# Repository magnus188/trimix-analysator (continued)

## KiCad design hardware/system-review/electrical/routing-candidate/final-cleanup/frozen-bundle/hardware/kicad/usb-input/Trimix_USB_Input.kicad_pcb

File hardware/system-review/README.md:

# Trimix whole-system review

**Prototype order status: HOLD.** The main PCB is fully routed and its frozen native DRC reports zero violations, unconnected items and schematic-parity issues. This package records the corrections and reproducible digital evidence; it is not a fabrication release. Factory processes, power-entry and protection evidence, and actual component interfaces must close before ordering. Physical charging, temperature, sealing, module-fit and reference-gas tests have not been performed.

The approved A3 exterior and the original PCBFit baseline are preserved. Mechanical review copies are **Trimix_Enclosure_A3_SystemReview** and the newer **Trimix_Enclosure_A3_ConnectorReview**. Purchasing, showcase work and production printing remain paused.

**2026-09-08 integration update:** the owner supplied a rear photograph with device-up confirmed and measured **13.4 mm from front glass to bare header tips**. The photo locates the Guition header and both USB ports at the top and the onboard SD socket at the left. The [photo registration](integration-photo/README.md) and [saved/reopened ConnectorReview v3](mechanical/connector-review/README.md) supersede the old illustrative connector locations. Complete mate allocations expose interference with the housing, carrier and holder; several straight cable plugs also leave inadequate wire-bend space. Local correction candidates are unadopted, and card service remains unqualified. Earlier v11 clearances do not prove fit of these interfaces. [Optional SD logging](software/sd-card/README.md) is implemented and digitally verified, using the onboard socket. The [bench-equipment record](lab-equipment.md) includes the confirmed multimeter, scope, DC PSU, DL24/P, DLA and FNB58.

The current main board is the reviewed `0962ad86` revision. Its charger bootstrap/REGN and CO-converter feedback/output-capacitor paths were shortened, while all 29 previously checked power/monitor paths were preserved. The [scoped power-layout review](electrical/routing-candidate/sensitive-layout-refinement/root-final-review/README.md) and independent manufacturing checks pass. The former routed revision remains archived. Regulator stability, noise, startup and thermal performance still require physical evidence.

The preserved **SystemReview v11 baseline** is saved and its native archive reopens with the same geometry, parameters and assembly associations. It retains the approved 85 × 180 × 43 mm exterior and exact CNC Kitchen insert models. Two carrier through-openings clear the revised rear components with complete local 2 mm material borders. Its selected component, connector, service, gas and fastener allocations pass at 85 and 87 mm widths, with the intended 85 mm design restored. Both oxygen reference configurations pass their bounded checks. See the [v11 checkpoint](mechanical/final-local-checkpoint/final-handoff.json). The later ConnectorReview findings above take precedence for actual Guition mating and cable-space decisions.

Both P4 firmware builds pass, alongside **53 normal and 53 sanitized host tests**, 98 repository checks and 22 static-analysis units. The [current source-bound software receipt](software/sd-card/evidence/receipt.json) includes SD fault/race tests, shared card/C6 controller lifecycle checks and real LVGL navigation regressions. The current schematic/firmware contract passes 70 assertions. CO requires fresh chamber temperature/humidity within its documented range; invalid conditions clear its displayed value while oxygen and helium stay independent. The [CO verification](software/co-environment/README.md) records scoped tests and [manufacturer use restrictions](electrical/co-module-use-review.md). The CO module remains experimental and cannot certify breathing-gas safety.

Analysis and calibration record results, raw samples and events automatically. The result log identifies both applied O2 and He calibration revisions; concurrent saves cannot mislabel those converted values. Card faults remain separate from NVS settings/calibration. SD safe eject, failed unmounts, session transitions and shutdown preparation have digital coverage. Real card operation, simultaneous radio traffic, memory headroom, write-current peaks and abrupt-power-loss behavior remain physical checks.

The preserved v11 STEP is a reference export with a documented limitation (CAD09): body count, bounds and selected surface/section checks pass, but strict volume comparison and one underlying-plane correspondence do not establish full per-body equivalence. It also predates the photo-correct Guition details. Native Fusion checkpoints carry their own revision and source scope; the old STEP is not the new connector model.

Eight preserved v11 PLA/PETG diagnostic projects for four printed parts pass 50 slice checks. These are fit-study files, with support removal, printed dimensions, retention, sealing and temperature tests still pending. They do not qualify the later proposed carrier or harness changes. [The acceptance ledger](acceptance.csv) separates completed digital work from the **13 remaining order-blocking gates**; those gates are related and are not 13 demonstrated hardware failures.

## Read the package

| Area | Starting document / evidence |
|---|---|
| Check-by-check acceptance and unresolved gates | [Acceptance ledger](acceptance.csv) — scoped statuses and the remaining order gates |
| Electrical interface, pin audits and calculations | [Electrical review](electrical/README.md), [logical interface](electrical/interface-contract.md) |
| Exact purchasing and assembly populations | [Part qualification ledger](electrical/part-qualification.csv) — unresolved entries are not purchasing approval |
| USB source rules and legacy limitations | [Current USB-IF source review](electrical/usb-default-current-review/README.md), [limiter alternatives and rejected assumptions](electrical/usb-protection-research/transient-options/README.md) |
| Screen cable and power entry | [Matched harness review](electrical/host-harness-review/README.md), [Guition power and service isolation](electrical/host-power-review/README.md) |
| Fabrication and routing | [Manufacturing constraints](electrical/manufacturing-and-routing.md), [selected stackup](electrical/stackup-review.md), fresh ERC/DRC JSON files in `electrical/` |
| Current main-board files | [Routed main delivery index](electrical/main-final/README.md) — Gerbers, drills, factory/manual BOMs, factory-only stencil, marking guide and selected-hole process map; order HOLD |
| Independent manufacturing-file review | [Final CAM review](electrical/main-final-independent/final-0962ad86/README.md) — 44 geometry/connectivity, 20 assembly-ledger, 12 preservation and 50 process checks pass; supplier process approval remains pending |
| Frozen routed main PCB | [Independent final power and ground review](electrical/routing-candidate/sensitive-layout-refinement/root-final-review/README.md) — 29 prior power/monitor paths retained, 35 local routes connected, one connected In1 reference and no lost ground contacts; physical performance remains unqualified |
| Completed controls checkpoint | [Parent review of the controls and power paths](electrical/routing-candidate/complete-controls-root-review/README.md) — preserved intermediate source before final assembly cleanup |
| Earlier routing evidence | [USB voltage-monitor and input-trace review](electrical/routing-candidate/monitor-root-review/README.md), [charger interrupt and I²C pull-ups](electrical/routing-candidate/cap-signal-reconnect/pullup-swap/README.md) — preserved intermediate checkpoints |
| Latest protection-chip escape | [CC route, retained voltage-setting circuit and ground checks](electrical/routing-candidate/set-cc-root-proposal/vippo-cc/README.md), [independent mask/drill and rule controls](electrical/vippo-process-review/native-v3-independent/README.md) — scoped proof; combined routing and factory process acceptance remain open |
| Copper-path diagnostic | [Method and limits](electrical/current-path-review/README.md), [preserved prior-board native path inventory](electrical/routing-candidate/final-cleanup/root-review/current-paths/paths.csv) — geometry sensitivities, not equivalent resistance or current ratings |
| Supplier questions prepared for later use | [Unsent process-review request](electrical/supplier-review-request.md) — no supplier contacted or order placed |
| Mechanical model and measurements | [Current enclosure review](mechanical/README.md), [final saved assembly](mechanical/final-local-checkpoint/final-handoff.json), [measurement checklist](mechanical/MEASUREMENTS.md) — provisional models stay labelled |
| Oxygen setup and calibration | [Oxygen implementation and UI evidence](software/oxygen/README.md) |
| OTA, storage and maintenance | [OTA review](software/ota/README.md), [concurrent-save evidence](software/ota/storage-maintenance-race-verification.json) |
| Onboard SD recording and shared controller | [Use, implementation and limits](software/sd-card/README.md), [final source-bound receipt](software/sd-card/evidence/receipt.json), [independent receipt binding check](integration-photo/sd-software-binding-check.json) |
| Production sensor, power and environmental acquisition | [Firmware integration](software/README.md), [input isolation and charging standby](software/power/input-isolation/README.md), [legacy attachment endurance](software/power/input-isolation/legacy-endurance-review/README.md) |
| Combined tests and firmware builds | `verification/` — source hashes must match the reported build and check |
| Before wiring and first power | [Measurement and bring-up checklist](electrical/measurement-and-bringup.md), [available instruments](lab-equipment.md), [blank test record](test-record-template.csv) |
| Step-by-step bench sequence | [Draft first-power procedure](first-power.md) — all physical stages pending |
| Illustrated logical wiring and measurements | [Six-page interface packet](interface-packet.pdf) - reference only; actual mating views still need confirmation |
| Passive tolerance/noise and power-model limits | [Analogue study](electrical/analogue-simulation/README.md), [power-model probe](electrical/power-simulation/README.md) |

## Acceptance language

Every check uses one of these outcomes:

- **Passed digitally:** the identified calculation, source inspection, simulation, host test or native CAD/EDA check passed for its stated inputs and revision.
- **Correction required:** a demonstrated failure or unfinished implementation remains.
- **Missing evidence:** a needed dimension, rating, manufacturer datum or process qualification is not established.
- **Physical testing pending:** bench, fit, thermal, gas, electrical or sealing evidence is still required.

A host test can prove that a bus error is rejected; it cannot prove the physical bus signal integrity. An interference check can prove that the supplied solids do not overlap; it cannot prove that an unmeasured plug has the correct solid model. ERC and DRC alone do not establish charging safety or gas accuracy.

## Decisions retained

Only one oxygen sensor is installed. Both differential input paths remain, with the approved J401/J402 order. Touchscreen selection persists separately from calibration; GPIO52/J301.7 is unused. A new or replacement cell requires calibration. No analogue voltage is treated as a digital sensor identity and measurement never changes inputs automatically.

The MD62 remains on a regulated 3.0 V excitation supply. ADS122C04 measurement electronics replace the two older ADCs; the gas sensors are retained. The four-layer main board and separate thin GCT USB daughterboard remain the manufacturing targets. The humidity module must actually contain a BME280; a BMP280 cannot measure humidity. The installed ZE07 module measures CO, not CO₂.

Current firmware deliberately inhibits charging and leaves the hardware charge-arm connection J104 open. Exact cell charge limits, holder/plug ratings and the temperature-sensing arrangement must be qualified before a charging profile is enabled. This commissioning restriction is explicit; charging has not been certified by the software or schematic review.

The ±0.2 percentage-point oxygen and ±0.5-point helium values are **unproven targets**. Characterization must include independent reference mixtures, the reference instrument's uncertainty, oxygen cross-effects, environment, repeated measurements and battery versus USB operation. No correction coefficients or accuracy claims are copied from another analyzer.

## Attribution and scope

The project remains inspired by [captainigloo/Trimix-analyzer](https://github.com/captainigloo/Trimix-analyzer). Existing repository attribution and licensing are retained; this review makes no repository-wide licensing change. Bosch's BME280 driver is vendored with its BSD-3-Clause notice and pinned source manifest. Host parser tests use the same cJSON source as the local ESP-IDF dependency, retaining its licence; device firmware links ESP-IDF's JSON component.

Manufacturer documents, downloaded reference models and third-party CAD are evidence with their own terms, not newly relicensed project designs. Source links and hashes accompany the respective electrical, mechanical and software checks.

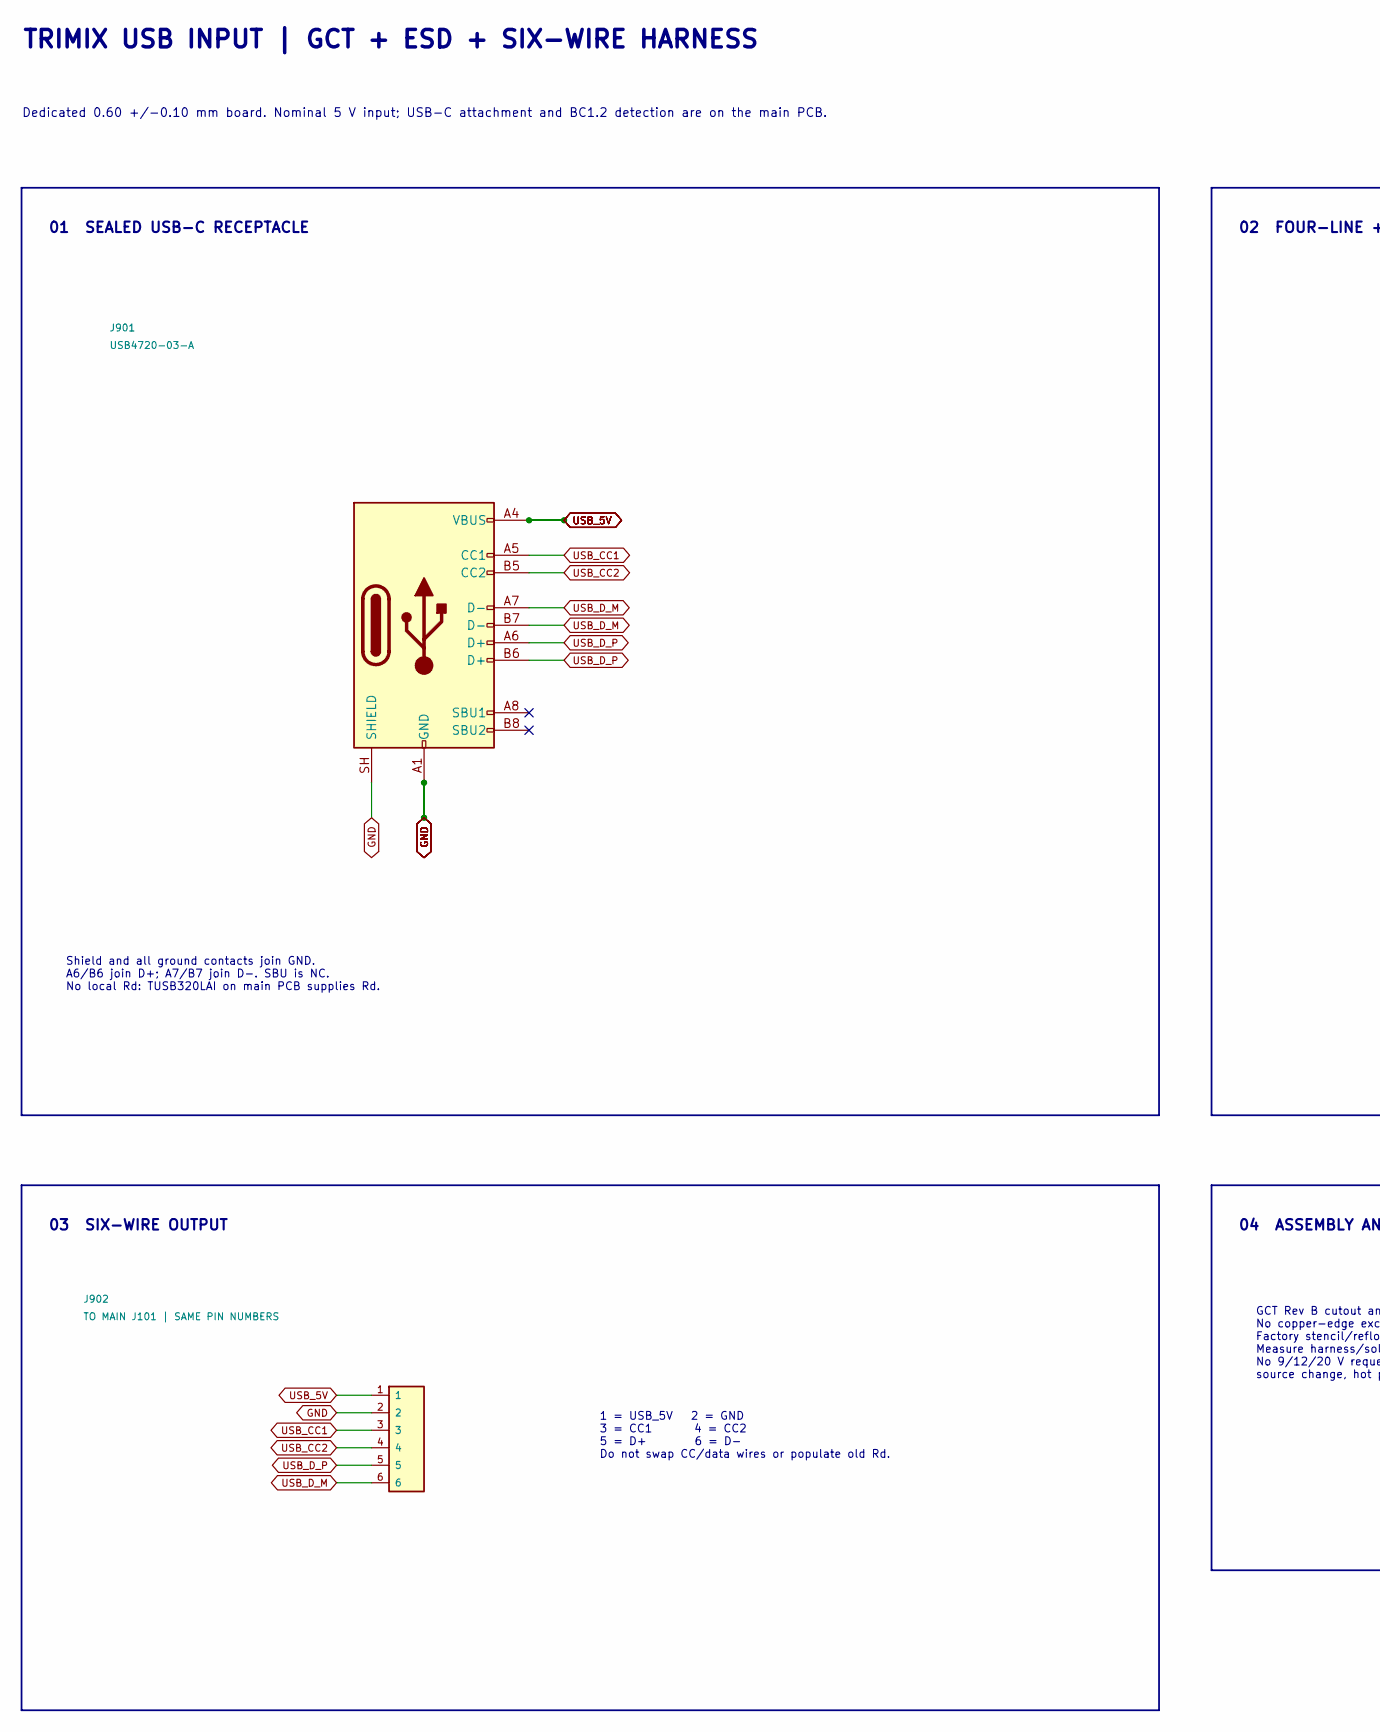
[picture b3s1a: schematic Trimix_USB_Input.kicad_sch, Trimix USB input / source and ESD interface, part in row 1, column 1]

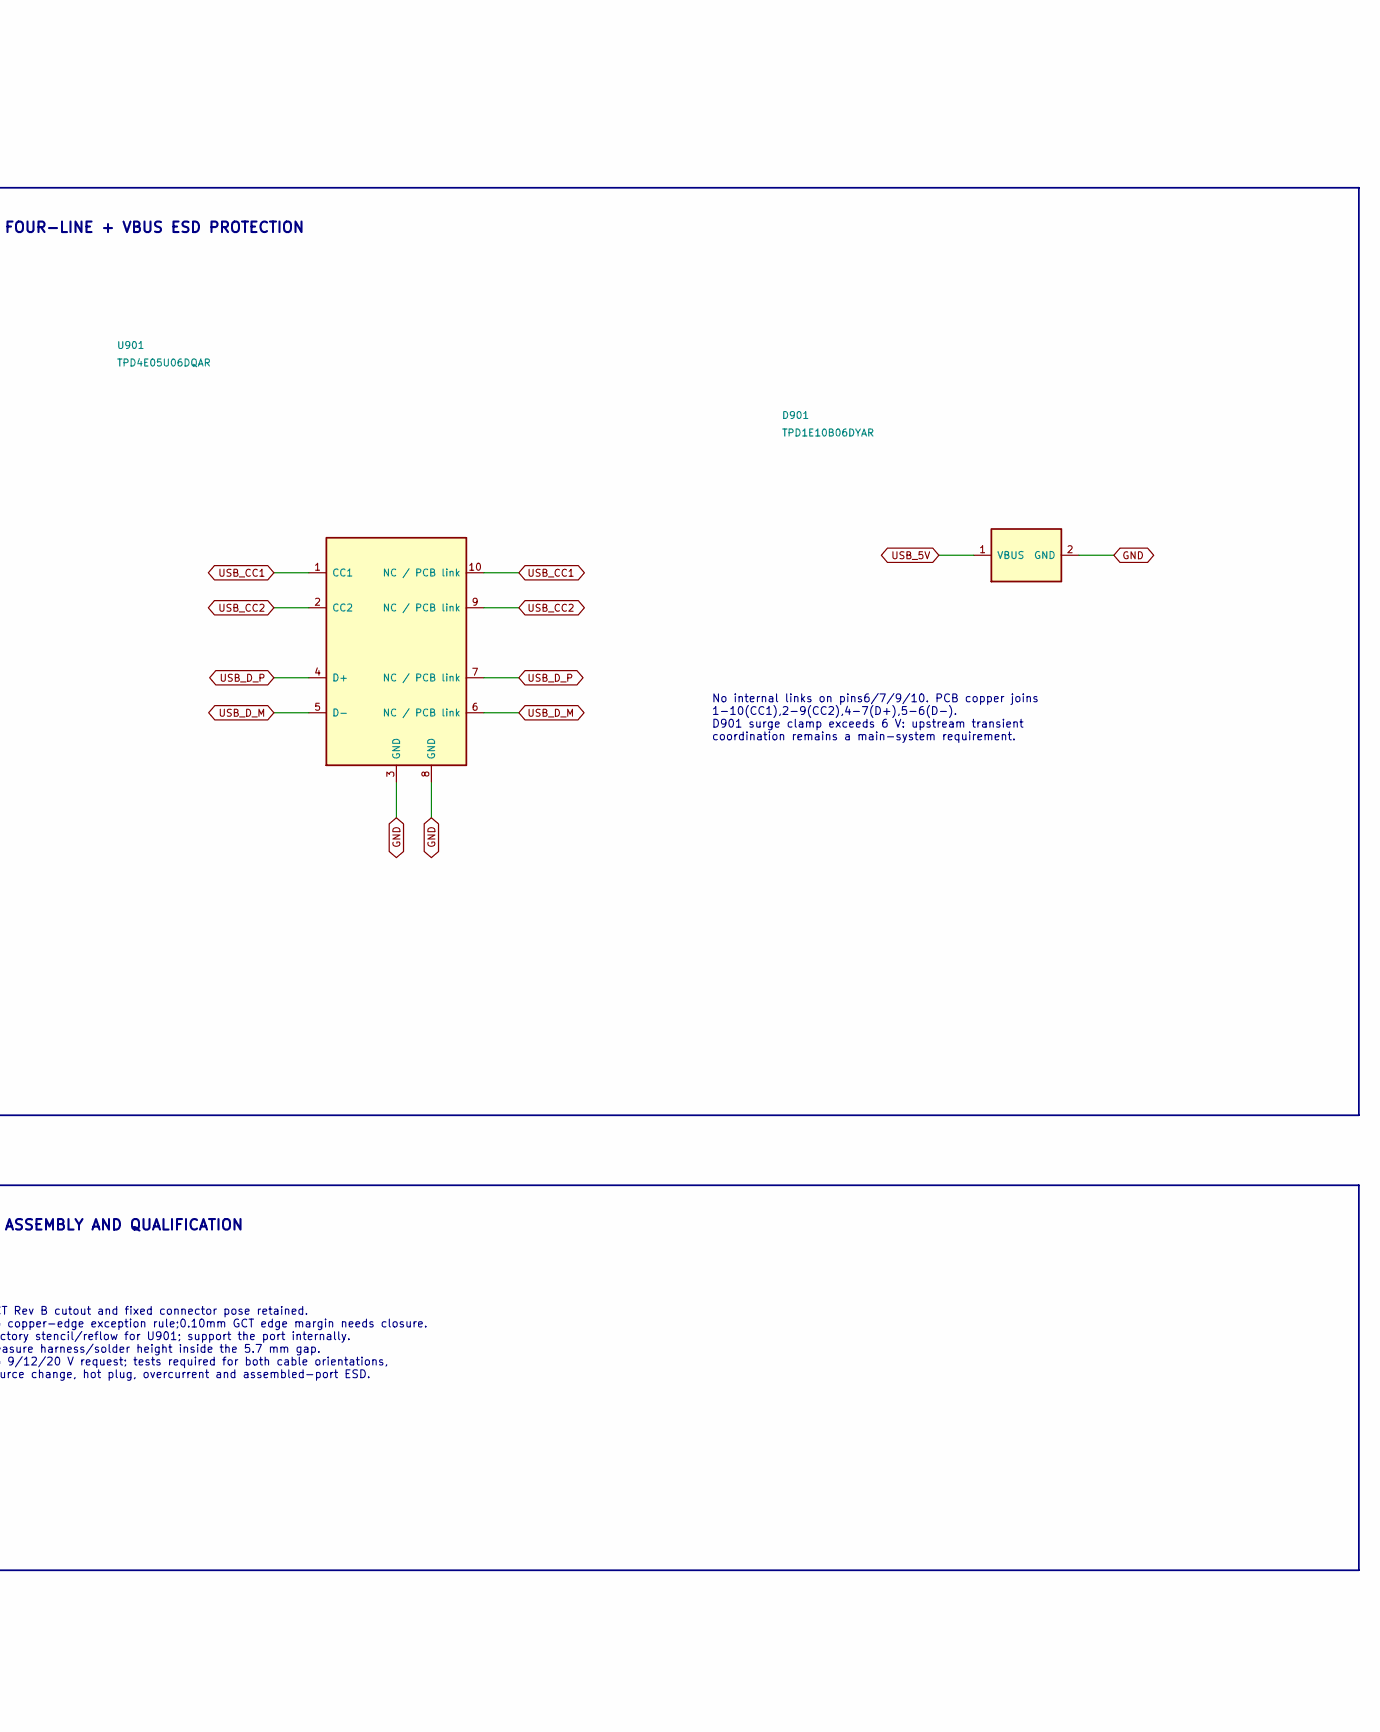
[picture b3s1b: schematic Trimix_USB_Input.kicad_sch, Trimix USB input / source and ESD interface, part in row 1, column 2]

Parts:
D901: TPD1E10B06DYAR; TI_DYA0002A; MPN TPD1E10B06DYAR
J901: USB4720-03-A; USB4720_RevB; MPN USB4720-03-A
J902: TO MAIN J101 | SAME PIN NUMBERS; USB_Harness_6P_P1.8mm
U901: TPD4E05U06DQAR; TI_DQA0010B; MPN TPD4E05U06DQAR

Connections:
GND: D901.2 (GND), J901.A1 (GND), J901.A12 (GND), J901.B1 (GND), J901.B12 (GND), J901.SH (SHIELD), J902.2, U901.3 (GND), U901.8 (GND)
USB_5V: D901.1 (VBUS), J901.A4 (VBUS), J901.A9 (VBUS), J901.B4 (VBUS), J901.B9 (VBUS), J902.1
USB_CC1: J901.A5 (CC1), J902.3, U901.1 (CC1), U901.10 (NC / PCB link)
USB_CC2: J901.B5 (CC2), J902.4, U901.2 (CC2), U901.9 (NC / PCB link)
USB_D_M: J901.A7 (D-), J901.B7 (D-), J902.6, U901.5 (D-), U901.6 (NC / PCB link)
USB_D_P: J901.A6 (D+), J901.B6 (D+), J902.5, U901.4 (D+), U901.7 (NC / PCB link)

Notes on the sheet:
TRIMIX USB INPUT | GCT + ESD + SIX-WIRE HARNESS
Dedicated 0.60 +/-0.10 mm board. Nominal 5 V input; USB-C attachment and BC1.2 detection are on the main PCB.
01 SEALED USB-C RECEPTACLE
02 FOUR-LINE + VBUS ESD PROTECTION
03 SIX-WIRE OUTPUT
04 ASSEMBLY AND QUALIFICATION
Shield and all ground contacts join GND. A6/B6 join D+; A7/B7 join D-. SBU is NC. No local Rd: TUSB320LAI on main PCB supplies Rd.
No internal links on pins6/7/9/10. PCB copper joins 1-10(CC1),2-9(CC2),4-7(D+),5-6(D-). D901 surge clamp exceeds 6 V: upstream transient coordination remains a main-system requirement.
1 = USB_5V 2 = GND 3 = CC1 4 = CC2 5 = D+ 6 = D- Do not swap CC/data wires or populate old Rd.
GCT Rev B cutout and fixed connector pose retained. No copper-edge exception rule;0.10mm GCT edge margin needs closure. Factory stencil/reflow for U901; support the port internally. Measure harness/solder height inside the 5.7 mm gap. No 9/12/20 V request; tests required for both cable orientations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

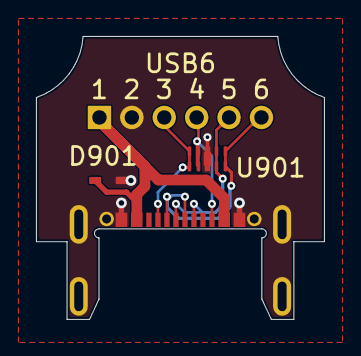
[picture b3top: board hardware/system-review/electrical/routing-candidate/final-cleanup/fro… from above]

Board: 2 copper layers, 16.0 x 15.7 mm, 4 parts (0 on the bottom side), 6 nets.

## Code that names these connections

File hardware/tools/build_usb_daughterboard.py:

"""A2.2: replace the unknown panel socket with a documented GCT USB board.

The integrated page excludes daughterboard parts from the main-board BOM.
The separate project includes those same four parts for its own PCB.
"""
from analyzer_sheet import *

DAUGHTER = HW/'pcb/usb-input'
NAME = 'Trimix_USB_Input'
FP = 'Trimix_Connectors:USB_C_GCT_USB4720-03-A'
WIRE_FP = 'Connector_Wire:SolderWire-0.25sqmm_1x02_P4.2mm_D0.65mm_OD1.7mm'


def rev(a):
    tb=child(a,'title_block');child(tb,'rev')[1]='A2.2';child(tb,'date')[1]='2026-09-06'


def build():
    s=Sheet('USB_Input',10,'USB input | GCT USB4720-03-A daughterboard',
      '5 V charging from USB-A or USB-C. Separate 0.60 mm USB PCB; main charger PCB remains 1.60 mm.')
    rev(s.a)
    s.box(20.32,48.26,226.06,114.3,'01  GCT SOCKET + TWO CC RESISTORS')
    s.box(254,48.26,147.32,114.3,'02  TWO-WIRE OUTPUT TO CHARGER')
    s.box(20.32,171.45,226.06,87.63,'03  CABLES, ORIENTATION & CURRENT')
    s.box(254,171.45,147.32,77.47,'04  MECHANICS & VERIFICATION')
    nets={p:'GND' for p in ['A1','A12','B1','B12','SH']}
    nets.update({p:'USB_5V' for p in ['A4','A9','B4','B9']})
    nets.update({'A5':'USB_CC1','B5':'USB_CC2'})
    nets.update({p:None for p in ['A6','A7','A8','B6','B7','B8']})
    sy=s.add('Connector:USB_C_Receptacle_USB2.0_16P','J901','GCT USB4720-03-A',53.34,93.98,nets,
      footprint=FP,on_board=False,in_bom=True,autowire=False,field_at=(29.21,64.77),
      properties={'Assembly':'USB daughterboard, not the main PCB',
        'PCB thickness':'0.60 +/- 0.10 mm per manufacturer drawing; mid-mount edge cutout required',
        'Status':'Selected replacement; not yet purchased or physically qualified',
        'Sealing':'GCT USB4720 connector IP67; enclosure/gasket installation requires separate validation',
        'Manufacturer':'GCT','MPN':'USB4720-03-A'})
    next(p for p in children(sy,'property') if p[1]=='Datasheet')[2]='https://gct.co/connector/usb4720'
    for ref,y,net in [('R901',83.82,'USB_CC1'),('R902',119.38,'USB_CC2')]:
        s.add('Device:R',ref,'5.1k / 1%',139.7,y,{'1':net,'2':'GND'},angle=90,
          footprint='Resistor_SMD:R_0603_1608Metric',on_board=False,in_bom=True,
          autowire=False,field_at=(124.46,88.9 if ref=='R901' else y-8.89),
          properties={'Assembly':'USB daughterboard; FIT one resistor per independent CC pin',
            'Purpose':'Passive sink attachment, present with battery disconnected and host off'})
        s.wire(s.pin(ref,2),(175.26,y));s.label('GND',(175.26,y),0)
        s.done.add((ref,'2'))
    s.wire(s.pin('J901','A5'),s.pin('R901',1));s.label('USB_CC1',(91.44,83.82),0)
    s.wire(s.pin('J901','B5'),(101.6,86.36),(101.6,119.38),s.pin('R902',1))
    s.label('USB_CC2',(101.6,113.03),90)
    s.wire(s.pin('J901','A4'),(210.82,78.74));s.label('USB_5V',(210.82,78.74),0)
    s.wire(s.pin('J901','A1'),(53.34,147.32));s.label('GND',(53.34,147.32),270)
    s.wire(s.pin('J901','SH'),(45.72,137.16),(53.34,137.16))
    for pin,net in nets.items():
        if net is not None:s.done.add(('J901',pin))
    s.done.update({('R901','1'),('R902','1')})
    s.text('CC1 and CC2 stay separate; fit both resistors.\nAll four VBUS and all four GND contacts are connected.\nData / SBU pins are unused. Shield connects to GND.\nThis is a passive 5 V sink, with no PD controller.',78.74,137.16,1.143)
    s.add('Connector_Generic:Conn_01x02','J902','TO MAIN PCB J101',342.9,83.82,
      {'1':'USB_5V','2':'GND'},footprint=WIRE_FP,on_board=False,in_bom=True,
      field_at=(304.8,68.58),properties={'Assembly':'USB daughterboard output pigtail pads; strain relief required',
        'Harness':'Pin 1 positive -> J101 pin 1; pin 2 return -> J101 pin 2. Verify physical polarity.'})
    s.text('J902 pin 1  ->  positive wire  ->  J101 pin 1\nJ902 pin 2  ->  return wire    ->  J101 pin 2',260.35,104.14,1.27)
    s.text('J901 / R901 / R902 / J902 belong to the USB PCB.\nThe main charger retains its two-wire input.\nUse soldered leads with enclosure strain relief;\nwire size and final mounting remain to be checked.',260.35,124.46,1.143)
    s.text('USB-C charger + C-to-C cable: separate Rd on CC1 / CC2\nallows source attachment in either plug orientation.\nTest both ends flipped, including an electronically marked cable.\n\nUSB-A charging adapter + A-to-C cable uses the same input.\nThe compliant legacy cable supplies Rp; do not add Rp here.\n\nBQ25895 D+/D- remain unused: nominal 500 mA INPUT setting.\nBattery charge current depends on available power and system load.\nNo 9/12/20 V PD request or 1.5/3 A detection is implemented.',25.4,187.96,1.27)
    s.text('GCT drawing: 0.60 +/- 0.10 mm PCB and edge cutout.\nDo not fit USB4720 directly to the 1.60 mm main board.\nProvide rigid support against cable insertion forces.\nIP67 connector does not certify the enclosure; charge dry.\n\nBefore power: verify CC1-GND and CC2-GND ~5.1k.\nWith ARM OPEN: verify 5 V in all cable orientations,\nincluding no battery / host off. Then qualify loaded\nvoltage, input current and inrush. Battery charging\ntests follow cell / holder / thermistor qualification.',259.08,186.69,1.143)
    s.finish()
    standalone(s.a)


def standalone(source):
    DAUGHTER.mkdir(exist_ok=True)
    a=copy.deepcopy(source);root=uid();child(a,'uuid')[1]=root
    tb=child(a,'title_block');child(tb,'title')[1]='Trimix USB daughterboard - GCT USB4720-03-A'
    for sy in children(a,'symbol'):
        ref=next(p[2] for p in children(sy,'property') if p[1]=='Reference')
        child(sy,'on_board')[1]=S('yes')
        sy[:]=[v for v in sy if tag(v)!='instances']
        sy.append(node('instances',node('project',NAME,node('path','/'+root,node('reference',ref),node('unit',1)))))
    a.append(node('sheet_instances',node('path','/',node('page','1'))))
    save(DAUGHTER/(NAME+'.kicad_sch'),a)
    pro=DAUGHTER/(NAME+'.kicad_pro')
    if not pro.exists():pro.write_text(json.dumps({'meta':{'filename':pro.name,'version':1}},indent=2)+'\n')
    for base,uri in [(P,'${KIPRJMOD}/Trimix_Connectors.pretty'),(DAUGHTER,'${KIPRJMOD}/../analyzer/Trimix_Connectors.pretty')]:
        path=base/'fp-lib-table'
        table=sx.loads(path.read_text()) if path.exists() else node('fp_lib_table',node('version',7))
        if not any(child(lib,'name')[1]=='Trimix_Connectors' for lib in children(table,'lib')):
            table.append(node('lib',node('name','Trimix_Connectors'),node('type','KiCad'),node('uri',uri),node('options',''),node('descr','GCT USB4720-03-A manufacturer drawing based footprint')))
        save(path,table)


def annotate():
    path=P/(PROJECT+'.kicad_sch');a=sx.loads(path.read_text());rev(a)
    for t in children(a,'text'):
        if t[1].startswith('A2.1 engineering'):t[1]=t[1].replace('A2.1','A2.2',1)
        if t[1].startswith('USB-C socket: separate CC resistors'):
            t[1]='GCT USB4720 + two CC resistors\nSeparate 0.60 mm USB daughterboard\n5 V input from USB-A or USB-C'
    save(path,a)
    path=P/'Charging.kicad_sch';a=sx.loads(path.read_text());rev(a)
    for t in children(a,'text'):
        if t[1].startswith('J101 receives 5 V from'):
            t[1]='J101 receives 5 V from the GCT USB daughterboard.\nJ902 -> two-wire harness -> J101 (same pin numbers).\nSee USB_Input, sheet 10; qualify before charging.'
    for sy in children(a,'symbol'):
        ps={p[1]:p for p in children(sy,'property')}
        if ps['Reference'][2]=='J101':ps['Value'][2]='FROM USB BOARD (2P)'
    save(path,a)


if __name__=='__main__':
    assert not DAUGHTER.exists(), 'USB daughterboard project exists; use a targeted edit to preserve user changes.'
    build();annotate()

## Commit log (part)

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2025-07-05 graph
2025-07-05 color in home screen
2025-07-05 added home screen
2025-07-05 new font
2025-07-05 fixing home
2025-07-05 axis on graph
2025-07-05 added settings
2025-07-05 o2 calibration
2025-07-05 wifi settings (not finished)
2025-07-05 restructure
2025-07-05 display settings
2025-07-05 settings manager
2025-07-05 sensor settings
2025-07-05 sqlite database
2025-07-05 navbar widget
2025-07-05 moved setup brightness script
2025-07-05 codebase fix 1
2025-07-05 workspace clean v2
2025-07-05 ui spacing issues
2025-07-06 converted to docker
2025-07-06 Add versioning system and update manager
    - Add version.py with semantic versioning (v0.1.0)
    - Add update_manager.py for GitHub release checking
    - Add update settings screen with UI
    - Add version_manager.py script for version bumping
    - Update main.py to show version in logs and window title
    - Update database_manager.py to use dynamic version
2025-07-06 feat: implement fully automated versioning and release workflow
    - Automated version bumping based on conventional commits
    - Automatic GitHub release creation with PR descriptions
    - Remove manual version management scripts
    - Clean CI/CD workflow that handles everything
    - PR template to guide release notes
    - Keep workspace clean - no manual versioning needed
2025-07-06 cleaning 🧼
2025-07-06 makefile
2025-07-06 ficing docker on rpi
2025-07-06 screen working
2025-07-06 unit tests
2025-07-06 ci cd testing
2025-07-06 feat: implement Docker-based firmware updates
    - Add GitHub Actions workflow for automated releases
    - Build multi-architecture Docker images (ARM64, ARMv7)
    - Enhance UpdateManager with Docker update support
    - Add manual update script for easy updates
    - Update docker-compose.yml for better update management
    - Add update progress tracking and UI improvements
2025-07-06 📝 Add docstrings to `dev`
    Docstrings generation was requested by @magnus188.
    * https://github.com/magnus188/trimix-analysator/pull/7#issuecomment-3042042676
    The following files were modified:
    * `main.py`
    * `run_tests.py`
    * `screens/home.py`
2025-07-06 fixed tests?
2025-07-06 fixing tests
2025-07-06 fixing tests?
2025-07-06 fixing ci tests?
2025-07-06 fixing tests? testing
2025-07-06 testsss
2025-07-06 removing failing test
2025-07-06 hjhj
2025-07-06 resa
2025-07-06 fdsa
2025-07-06 Dev test pr (#9)
    * 📝 Add docstrings to `dev`
    Docstrings generation was requested by @magnus188.
    * https://github.com/magnus188/trimix-analysator/pull/7#issuecomment-3042042676
    The following files were modified:
    * `main.py`
    * `run_tests.py`
2025-07-06 tetsing
2025-07-06 fixing make run
2025-07-06 removing docker due to lagging
2025-07-06 auto release
2025-07-06 Feature: removing lag (#10)
    * 📝 Add docstrings to `dev`
    Docstrings generation was requested by @magnus188.
    * https://github.com/magnus188/trimix-analysator/pull/7#issuecomment-3042042676
    The following files were modified:
    * `main.py`
    * `run_tests.py`
2025-07-06 fixed nav buttons
2025-07-07 celan up
2025-07-07 analyser store data
2025-07-07 ppm safety settings
2025-07-14 convert to eps32
2025-07-31 Initial plan
2025-07-31 Add complete ESP32-S3 project structure with LVGL UI
2025-07-31 Complete ESP32-S3 conversion with settings screen and documentation
2025-08-07 Create comprehensive GitHub Copilot instructions with validated commands and accurate timing
2025-08-10 converting to esp32 only, removing all python files
2025-08-10 Fix ESP32-8048S043 configuration and add development mode with better error handling
2025-08-10 Fix ESP32-8048S043 build issues: LVGL v9.2.0 config, pin conflicts, and library updates
2025-08-10 Fix ESP32-S3 GPIO_DIR_MASK compilation errors by migrating from TFT_eSPI to Arduino_GFX
2025-08-11 lvgl showing but flickering
2025-09-04 Complete ESP32 conversion with LVGL GUI and sensor interface
2025-09-04 Convert ESP32 display from landscape to portrait orientation (480x800)
2025-09-04 Remove all old Python project files, keep only ESP32 implementation
2025-09-04 Set up PlatformIO configuration for ESP32 project
2025-09-04 Remove PlatformIO configuration and restore original ESP-IDF project structure
2025-09-04 flattened
2025-09-04 demo works
2025-09-04 works now!
2025-09-04 portrait
2025-09-04 converted to c++ and restructuring
2025-09-06 divided into seperate UI screens
2025-09-06 custom font
2025-09-06 reorganize + copmonents
2025-09-06 cleanup
2025-09-06 bigger font
2025-09-06 settings buttons
2025-09-06 wifi but broken
2025-09-06 adding software update
2025-12-24 wifi
2025-12-24 settings screen
2025-12-24 wifi and OTA
2025-12-24 dive planner
2025-12-25 navbar changes
2025-12-25 CI/CD
2025-12-25 feat: wifi fix
2025-12-28 screen bug fixed
2025-12-28 number keypad
2025-12-29 fix: scrolling issue etc
2025-12-29 Dev (#21)
    * cleanup
    * feat: wifi fix
    * screen bug fixed
    * number keypad
    * fix: scrolling issue etc
2025-12-29 chore: bump version to 0.1.1 [skip ci]
2025-12-29 feat: OTA update
